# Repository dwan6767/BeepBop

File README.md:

# BeepBop

Minimalist LoRa hardware experiments. Schematics, firmware, and logs for small-form-factor devices.

### Device Chain

- **[Hypergrey](hypergrey/README.md)**: A USB-based LoRa terminal designed for direct plugging and long-distance transceiving.

### Status
- Active development.

### Disclaimer
RF equipment. Operate within local legal limits.

---
[dwan6767](https://github.com/dwan6767)

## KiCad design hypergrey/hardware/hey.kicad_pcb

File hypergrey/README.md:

# Hypergrey

> USB-based LoRa terminal for long-distance transceiving.

Hypergrey is an open-hardware LoRa transceiver in a compact dongle/terminal form factor. Plug it directly into any host machine (PC, Raspberry Pi, SBC) via USB to send and receive serial data over long-range LoRa links without extra wiring or breakout boards.

---

## Highlights

- **Direct USB Interface:** Plug-and-play serial connection for any terminal or host software.
- **Long-Distance Transceiver:** Tuned Sub-GHz LoRa RF frontend for robust telemetry and remote messaging.
- **Compact & Portable:** Engineered as a single integrated stick/dongle.
- **Open Hardware:** Schematics, board layouts, and firmware are open for learning, modification, and reproduction.

---

## Visuals & Hardware Layout

### Hardware Build Overview

*Physical Hypergrey board prototype.*

*Close-up of the USB LoRa terminal module.*

---

## Hardware Specifications

| Spec | Detail |
| :--- | :--- |
| **Form Factor** | USB dongle / terminal |
| **Connectivity** | USB Type-C / USB-A |
| **RF Transceiver** | LoRa Sub-GHz (868 / 915 MHz / 433 MHz) |
| **Interface** | Virtual COM / Serial UART |
| **Antenna** | SMA / IPEX / PCB trace |
| **License** | Open Hardware (CERN-OHL / MIT) |

---

## Directory Structure

```
hypergrey/
├── images/       # Hardware photos, schematics, and diagrams
├── hardware/     # KiCad schematics, PCB layout, and gerbers
└── firmware/     # Source code and precompiled binaries
```

---

*Part of the [BeepBop](https://github.com/dwan6767/BeepBop) device chain.*

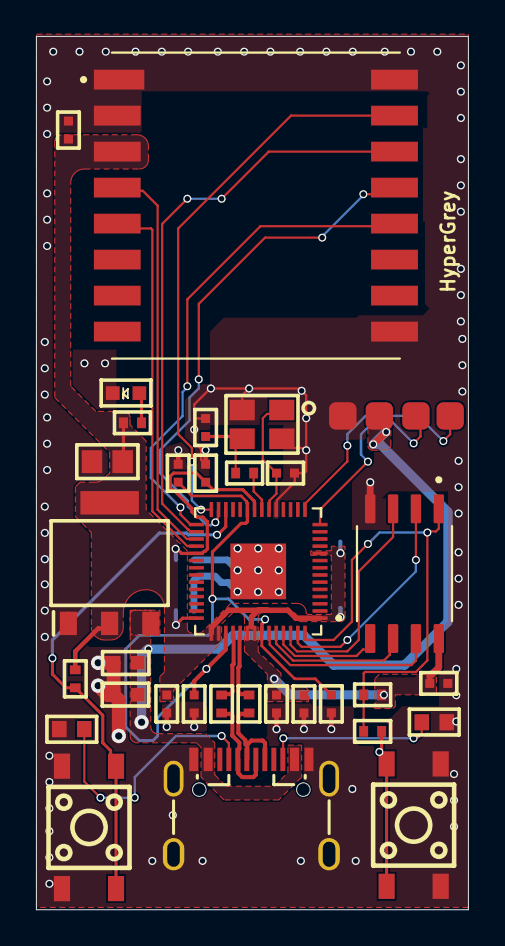
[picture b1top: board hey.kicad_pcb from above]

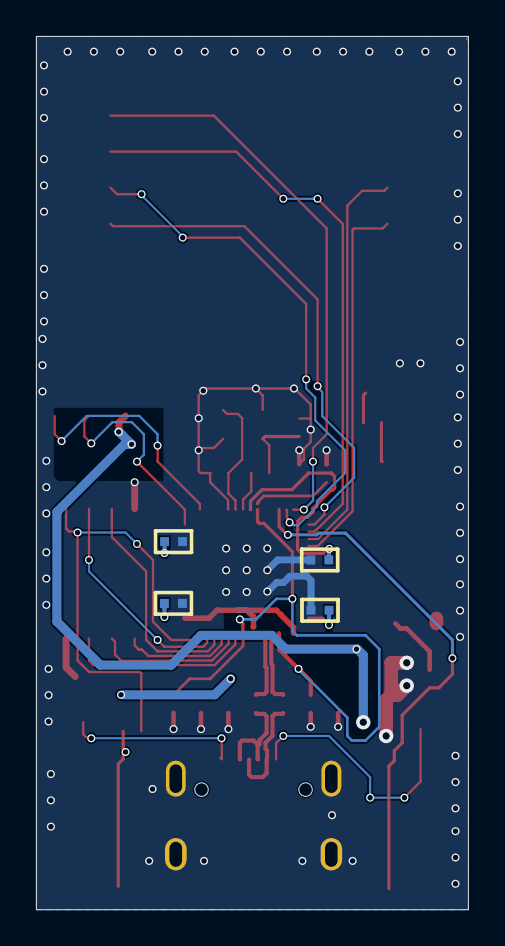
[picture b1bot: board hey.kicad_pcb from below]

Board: 2 copper layers, 24.0 x 48.5 mm, 36 parts (4 on the bottom side), 28 nets.

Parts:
C1, C17: Cap; CAPC0603
C2: CAPC0805
C3, C4, C5, C6, C7, C8, C9, C10, C11, C12, C13, C14, C15, C16, C18: Cap; CAPC0402
J1: TYPE-C
LED1: LED2; led_0603
R1, R2, R3, R4, R5, R6, R7: RES; RESC0402
R8, R9: Resistor; RESC0603
SW1, SW2: UK-B0206-G5-160-JZ; Button 4.5*4.5*5
U1: AMS1117
U2: W25Q128JVSIQ; SOIC127P790X216-8N
U3: QFN40P700X700X90-57N
U4: RA-02_LORA; MODULE_RA-02_LORA
X1: CRYSTAL_1; Crystal_3225

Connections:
1.1V: C3.1, C4.1, C14.2, U3.23, U3.45, U3.50
+3.3V: C2.1, C5.1, C6.1, C7.2, C8.1, C9.1, C10.1, C11.1, C12.1, C13.1, C18.1, R1.1, R2.2, R4.2, U1.2, U1.4, U2.8, U3.1, U3.10, U3.22, U3.33, U3.42, U3.43, U3.44, U3.48, U3.49, U4.3
+5V: C1.2, C17.1, J1.A4, J1.A9, U1.3
BOOT: R3.2, SW1.1, SW1.4
CLK: U2.6, U3.52
CS: R2.1, R3.1, U2.1, U3.56
GND: C1.1, C2.2, C3.2, C4.2, C5.2, C6.2, C7.1, C8.2, C9.2, C10.2, C11.2, C12.2, C13.2, C14.1, C15.2, C16.2, C17.2, C18.2, J1.A1, J1.A12, J1.S1, J1.S2, J1.S3, J1.S4, LED1.2, R8.2, R9.2, SW1.2, SW1.3, SW2.2, SW2.3, U1.1, U2.4, U3.19, U3.57, U4.1, U4.2, U4.9, U4.16, X1.2, X1.4
IO0: U2.5, U3.53
IO1: U2.2, U3.55
IO2: U2.3, U3.54
IO3: U2.7, U3.51
NetC16_1: C16.1, R7.1, X1.3
NetJ1_A5: J1.A5, R8.1
NetJ1_B5: J1.B5, R9.1
NetLED1_1: LED1.1, R1.2
NetU3_27: U3.27, U4.13
NetU3_28: U3.28, U4.15
NetU3_29: U3.29, U4.12
NetU3_30: U3.30, U4.14
NetU3_31: U3.31, U4.4
NetU3_32: U3.32, U4.5
RST: R4.1, SW2.1, SW2.4, U3.26
USB_N: J1.A7, J1.B7, R5.2
USB_P: J1.A6, J1.B6, R6.1
USB__N: R5.1, U3.46
USB__P: R6.2, U3.47
XIN: C15.1, U3.20, X1.1
XOUT: R7.2, U3.21
